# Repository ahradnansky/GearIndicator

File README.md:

# GearIndicator

Gear Indicator for Kawasaki and Suzuki bikes using communication with ECU over ISO9141 / K-Bus protocol

This project I implemented couple of years ago. We bought Kawasaki Z750 that time and needed to have gear indication
which apparently Kawasaki didn't have installed. About 30 of these were installed on different Kawasaki an Suzuki bikes
in following years. Just dont want this project to throw away and forget. Maybe someone will like it.

## Resources

Project has hardware and software part. Content of Resources directory:

### &emsp;__Eagle

&emsp;Hardware scheme and PCB created in CadSoft Eagle (Autodek Eagle now).
&emsp;Indicator has 2 PCBs. DISP - PCB with 7 segment display and Controller. PWR - PCB with voltage regulator and ISO9141 interface IC.

### &emsp;__HWcomponents

&emsp;Datasheets of all HW components used.

### &emsp;__Manuals

&emsp;We have created couple of installation manuals for Kawasaki and Suzuki bikes. Existing PDFs are here.

### &emsp;__SketchUp

&emsp;3D model of the final product. Prepared to be placed to the potting box. Final product with soldered cable was placed into potting box (type and data in _HWcomponents folder).
&emsp;Then Araldite expoxy was used for potting. Here you will find PCB 3D model as well as 3D model of the completed device.

# Source code

&emsp;Source code in C. Design is based on ATmega328p controller. Atmel Studio (Microchip Studio now) was used as a development IDE at the begining. Later transfeter to PlatformIO - as it is now.

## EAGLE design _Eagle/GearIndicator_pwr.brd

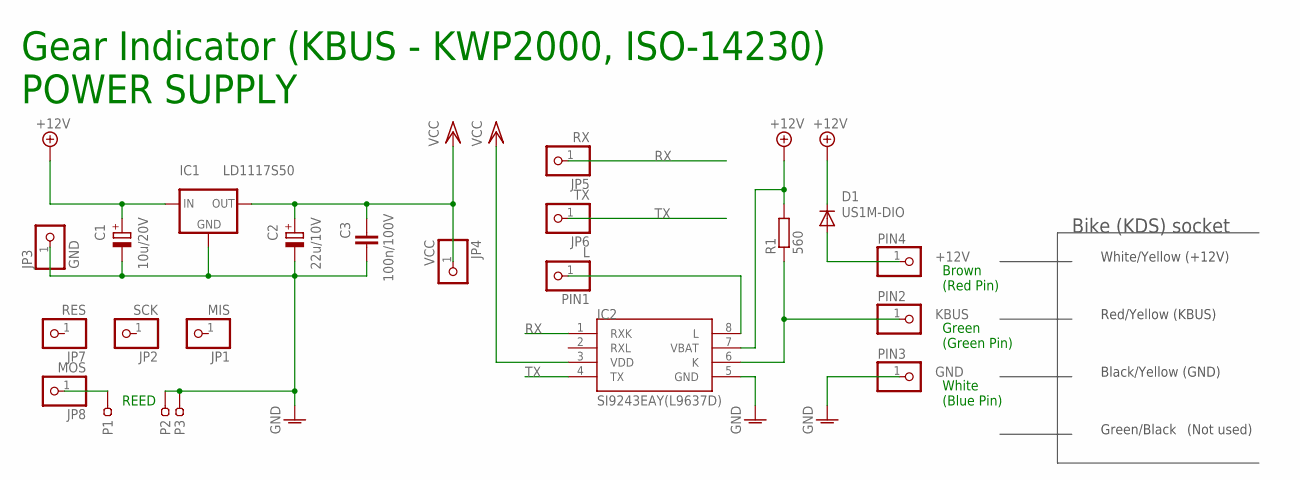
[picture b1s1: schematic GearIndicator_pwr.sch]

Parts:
C1: 10u/20V; CT3216
C2: 22u/10V; CT3216
C3: 100n/100V; C1206
D1: US1M-DIO; DO-214AC
IC1: LD1117S50; SOT223
IC2: SI9243EAY(L9637D); SO08
JP1: MIS; 1X01
JP2: SCK; 1X01
JP3: GND; 1X01
JP4: VCC; 1X01
JP5: RX; 1X01
JP6: TX; 1X01
JP7: RES; 1X01
JP8: MOS; 1X01
P1, P2, P3: SMD2; SMD_2X1
PIN1: L; PIN1
PIN2: KBUS; PIN1
PIN3: GND; PIN1
PIN4: +12V; PIN1
R1: 560; R1206

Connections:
+12V: C1.+, D1.C, IC1.3 (IN), IC2.7 (VBAT), R1.2
GND: C1.-, C2.-, C3.2, IC1.1 (GND), IC2.5 (GND), JP3.1, P2.P$1, P3.P$1, PIN3.1
unnamed: D1.A, PIN4.1
unnamed: IC2.8 (L), PIN1.1
unnamed: IC2.6 (K), PIN2.1, R1.1
unnamed: JP8.1, P1.P$1
RX: IC2.1 (RXK), JP5.1
TX: IC2.4 (TX), JP6.1
VCC: C2.+, C3.1, IC1.2 (OUT), IC2.3 (VDD), JP4.1

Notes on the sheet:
White/Yellow (+12V)
Red/Yellow (KBUS)
Black/Yellow (GND)
Gear Indicator (KBUS - KWP2000, ISO-14230) POWER SUPPLY
Brown (Red Pin)
Green (Green Pin)
White (Blue Pin)
Bike (KDS) socket
Green/Black
(Not used)
REED

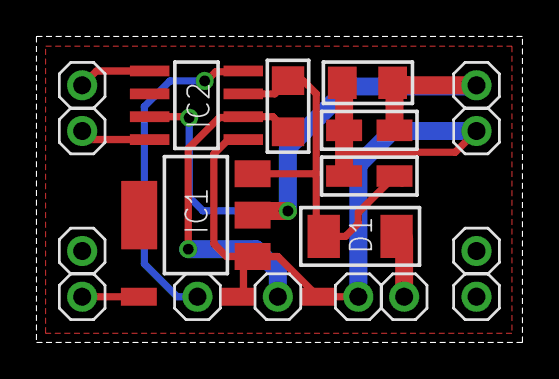
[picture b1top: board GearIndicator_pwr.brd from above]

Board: 2 copper layers, 27.0 x 17.0 mm, 22 parts (0 on the bottom side), 9 nets.

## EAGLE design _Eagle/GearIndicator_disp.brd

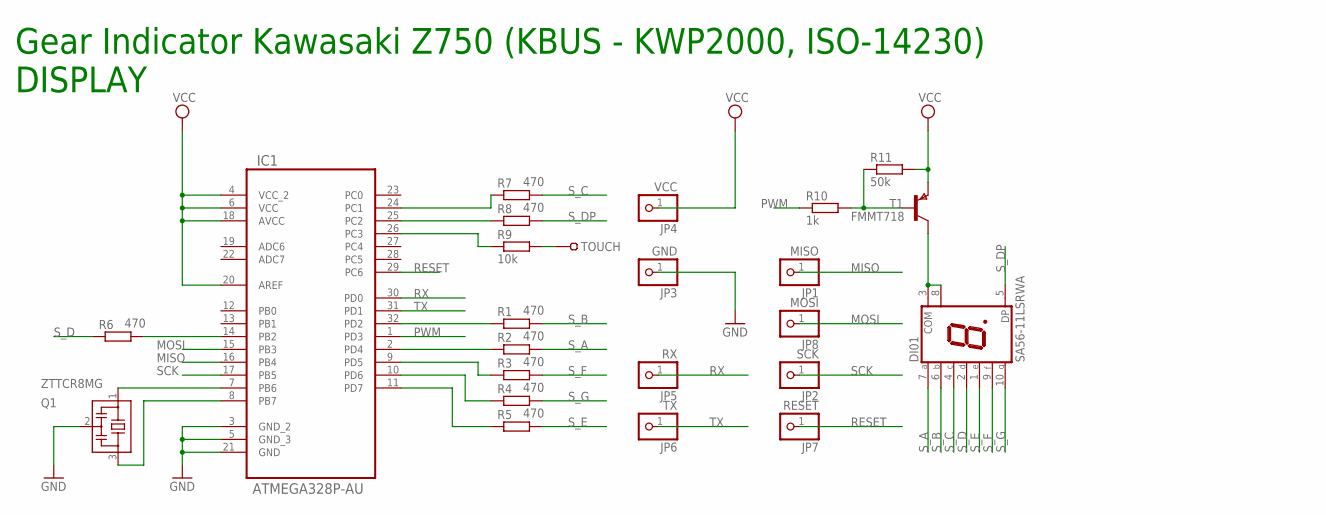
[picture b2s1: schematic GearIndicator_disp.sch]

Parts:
DI01: SA56-11LSRWA; SA56-11
IC1: ATMEGA328P-AU; QFP80P900X900X120-32N
JP1: MISO; PIN1
JP2: SCK; PIN1
JP3: GND; PIN1
JP4: VCC; PIN1
JP5: RX; PIN1
JP6: TX; PIN1
JP7: RESET; PIN1
JP8: MOSI; PIN1
Q1: ZTTCR8MG; ZTTCR
R1, R2, R3, R4, R5, R6, R7, R8: 470; R0603
R9: 10k; R0603
R10: 1k; R0603
R11: 50k; R0603
T1: FMMT718; SOT-23
TOUCH: SMD1; SMD_2X2

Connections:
GND: IC1.3 (GND_2), IC1.5 (GND_3), IC1.21 (GND), JP3.1, Q1.2
MISO: IC1.16 (PB4), JP1.1
MOSI: IC1.15 (PB3), JP8.1
unnamed: IC1.7 (PB6), Q1.1
unnamed: IC1.8 (PB7), Q1.3
unnamed: DI01.3 (COM), DI01.8 (COM), T1.1 (C)
unnamed: IC1.24 (PC1), R7.1
unnamed: IC1.25 (PC2), R8.1
unnamed: IC1.11 (PD7), R5.1
unnamed: IC1.14 (PB2), R6.1
unnamed: IC1.32 (PD2), R1.1
unnamed: IC1.2 (PD4), R2.1
unnamed: IC1.9 (PD5), R3.1
unnamed: R10.2, R11.1, T1.3 (B)
unnamed: IC1.26 (PC3), R9.1
unnamed: R9.2, TOUCH.P$1
unnamed: IC1.10 (PD6), R4.1
PWM: IC1.1 (PD3), R10.1
RESET: IC1.29 (PC6), JP7.1
RX: IC1.30 (PD0), JP5.1
SCK: IC1.17 (PB5), JP2.1
S_A: DI01.7 (A), R2.2
S_B: DI01.6 (B), R1.2
S_C: DI01.4 (C), R7.2
S_D: DI01.2 (D), R6.2
S_DP: DI01.5 (DP), R8.2
S_E: DI01.1 (E), R5.2
S_F: DI01.9 (F), R3.2
S_G: DI01.10 (G), R4.2
TX: IC1.31 (PD1), JP6.1
VCC: IC1.4 (VCC_2), IC1.6 (VCC), IC1.18 (AVCC), IC1.20 (AREF), JP4.1, R11.2, T1.2 (E)

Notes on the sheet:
Gear Indicator Kawasaki Z750 (KBUS - KWP2000, ISO-14230) DISPLAY

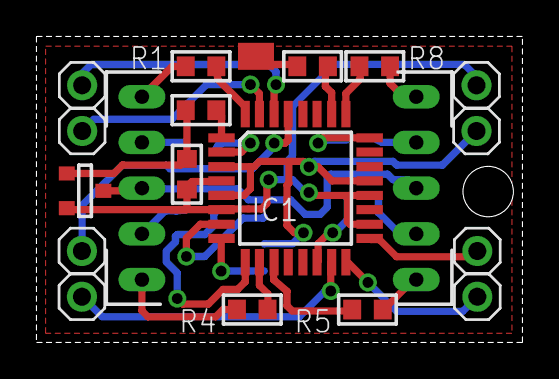
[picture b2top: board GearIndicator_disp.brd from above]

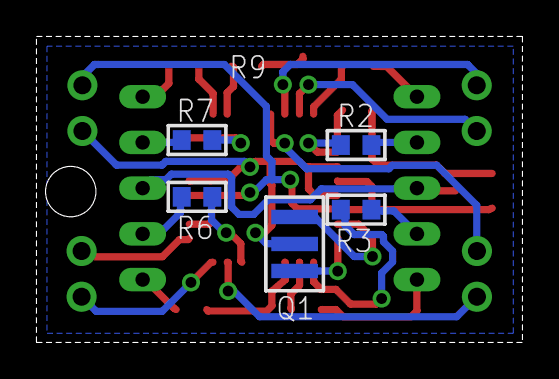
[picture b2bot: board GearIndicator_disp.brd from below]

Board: 2 copper layers, 27.0 x 17.0 mm, 24 parts (5 on the bottom side), 31 nets.

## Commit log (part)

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2022-04-04 Master commit
2022-04-26 Added LICENSE file
